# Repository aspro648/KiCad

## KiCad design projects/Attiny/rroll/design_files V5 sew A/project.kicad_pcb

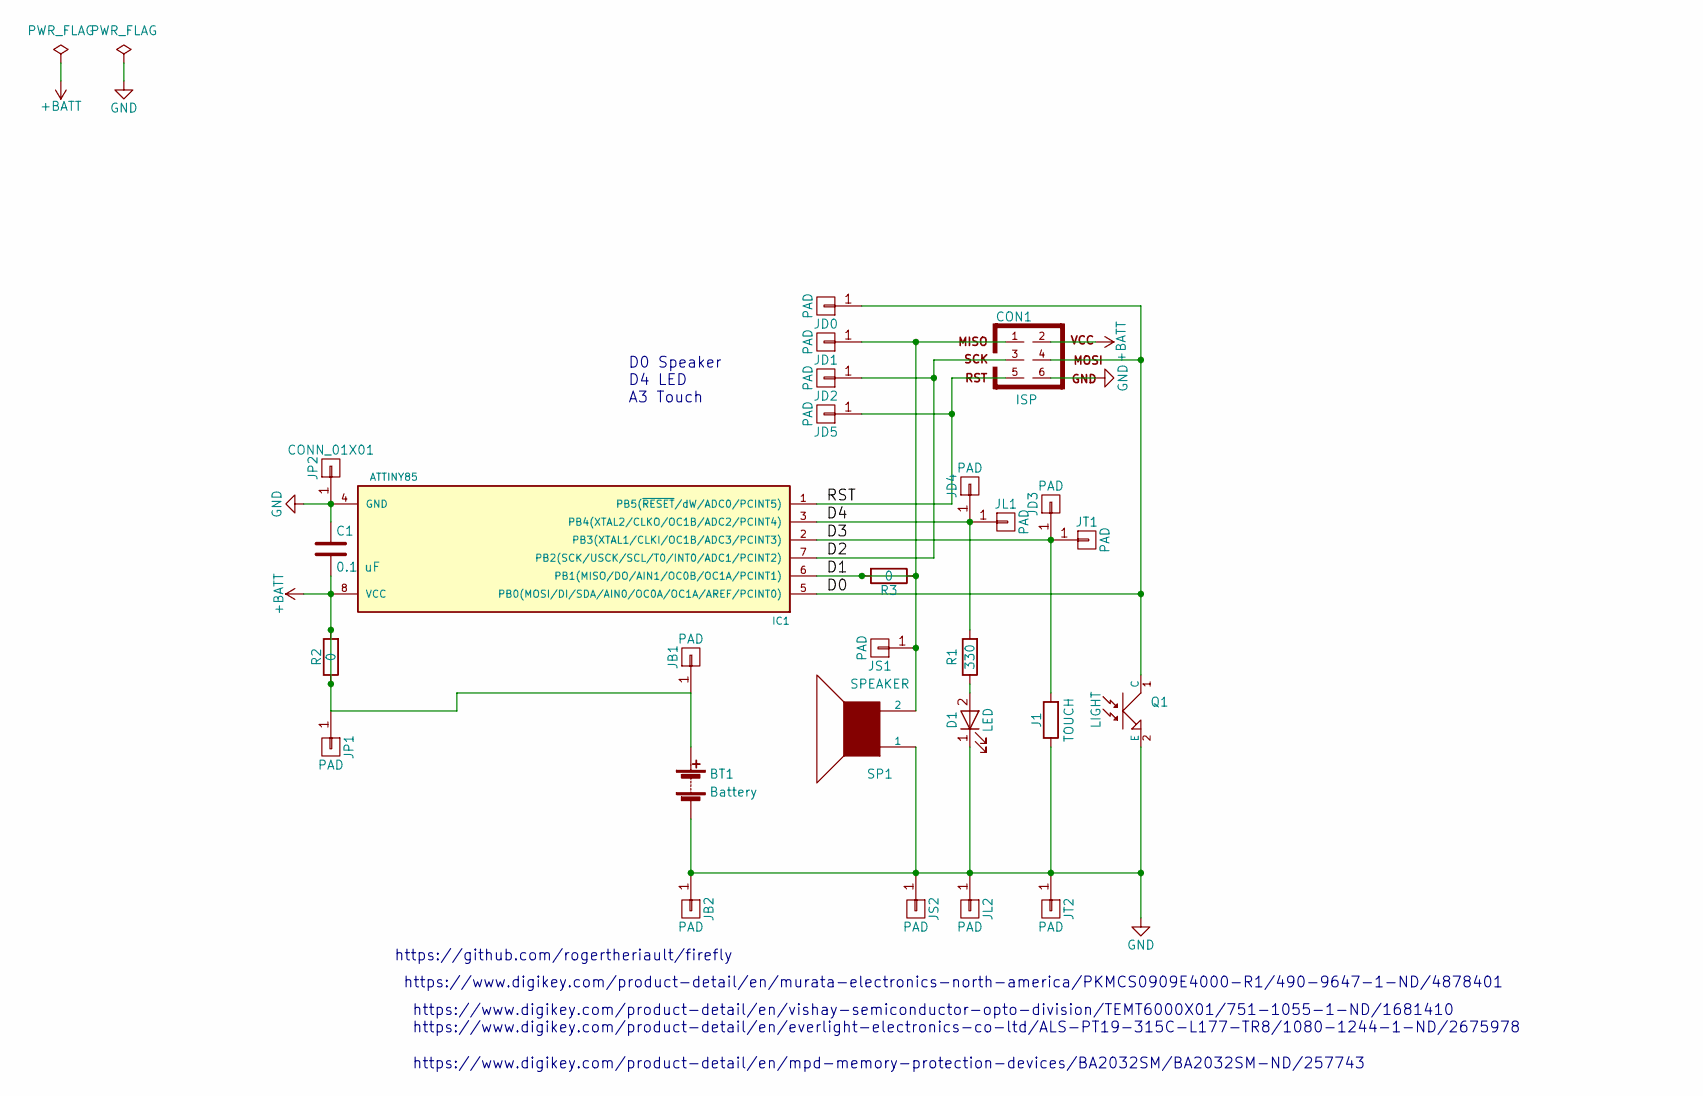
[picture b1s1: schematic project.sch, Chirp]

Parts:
BT1: Battery; BATT_CR2032_SMD
C1: 0.1 uF; C_1206
CON1: ISP; Pin_Header_Straight_2x03_Pitch2.54mm
D1: LED; LED_1206
IC1: ATTINY85; SOIJ-8_5.3x5.3mm_Pitch1.27mm
J1: TOUCH; R_1206_HandSoldering
JB1, JB2: PAD; SewPad
JD0, JD1, JD2, JD3, JD4, JD5: PAD; SewPad
JL1, JL2: PAD; SewPad
JP1: PAD; SewPad
JP2: CONN_01X01; SewPad
JS1, JS2: PAD; SewPad
JT1, JT2: PAD; SewPad
Q1: LIGHT; PhotoDiode_SMD-DIL2_4.5x4
R1: 330; R_1206
R2, R3: 0; R_1206
SP1: SPEAKER; PS1240_piezo

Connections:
+BATT: BT1.1 (+), C1.2, CON1.2, IC1.8 (VCC), JB1.1, JP1.1, R2.1, R2.2; also elsewhere on the board
/D3: IC1.2 (PB3(XTAL1/CLKI/OC1B/ADC3/PCINT3)), J1.2, JD3.1, JT1.1
/D4: IC1.3 (PB4(XTAL2/CLKO/OC1B/ADC2/PCINT4)), JD4.1, JL1.1, R1.2
/MISO: CON1.1, IC1.6 (PB1(MISO/DO/AIN1/OC0B/OC1A/PCINT1)), JD1.1, JS1.1, R3.1, R3.2, SP1.2
/MOSI: CON1.4, IC1.5 (PB0(MOSI/DI/SDA/AIN0/OC0A/OC1A/AREF/PCI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), JD0.1, Q1.1 (C)
/RST: CON1.5, IC1.1 (PB5(~RESET~/dW/ADC0/PCINT5)), JD5.1
/SCK: CON1.3, IC1.7 (PB2(SCK/USCK/SCL/T0/INT0/ADC1/PCINT2)), JD2.1
GND: BT1.2 (-), C1.1, CON1.6, D1.1 (K), IC1.4 (GND), J1.1, JB2.1, JL2.1, JP2.1, JS2.1, JT2.1, Q1.2 (E), SP1.1; also elsewhere on the board
unnamed: D1.2 (A), R1.1

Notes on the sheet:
D0 Speaker D4 LED A3 Touch
https://github.com/rogertheriault/firefly
https://www.digikey.com/product-detail/en/murata-electronics-north-america/PKMCS0909E4000-R1/490-9647-1-ND/4878401
https://www.digikey.com/product-detail/en/vishay-semiconductor-opto-division/TEMT6000X01/751-1055-1-ND/1681410 https://www.digikey.com/product-detail/en/everlight-electronics-co-ltd/ALS-PT19-315C-L177-TR8/1080-1244-1-ND/2675978
https://www.digikey.com/product-detail/en/mpd-memory-protection-devices/BA2032SM/BA2032SM-ND/257743

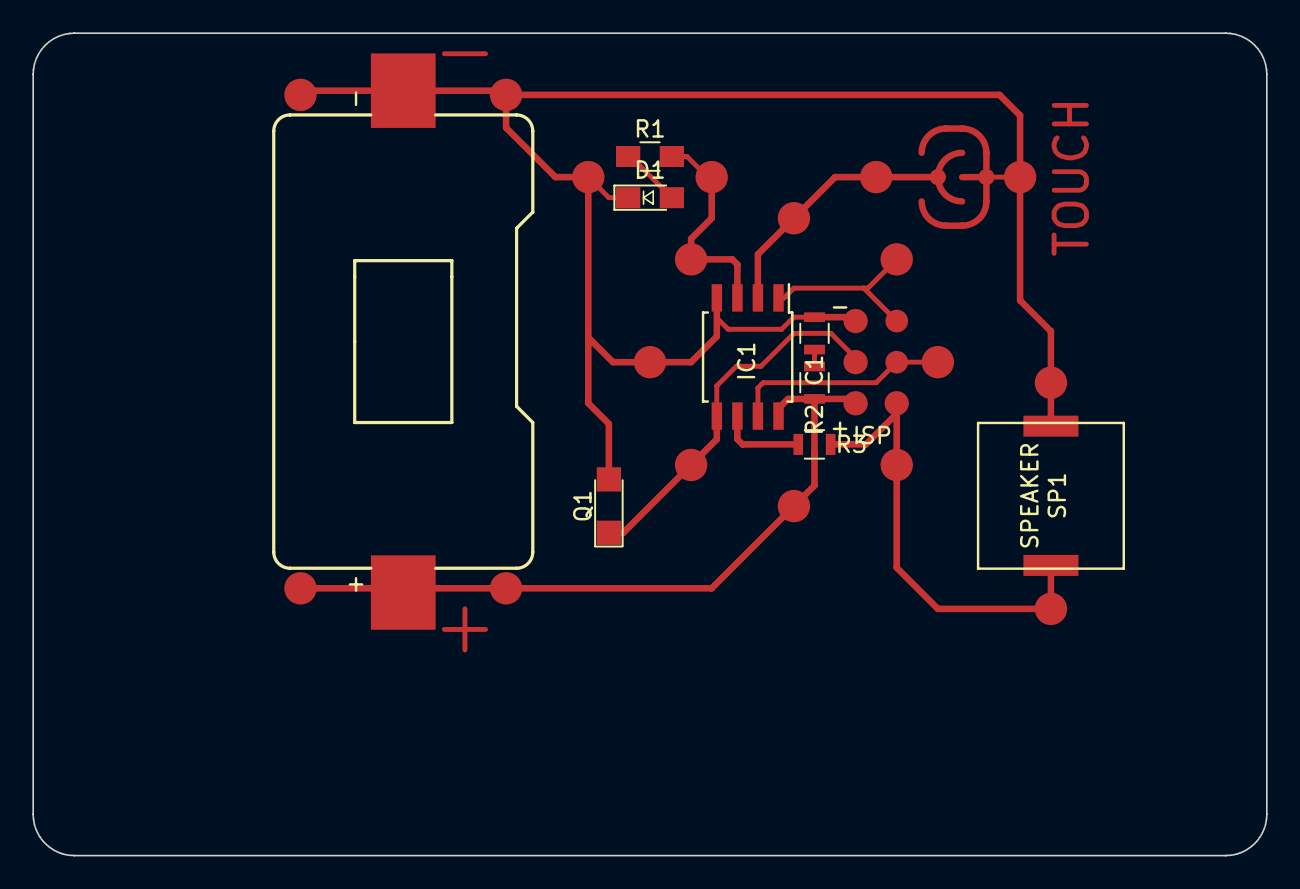
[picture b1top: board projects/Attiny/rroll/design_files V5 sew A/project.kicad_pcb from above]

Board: 2 copper layers, 76.2 x 50.8 mm, 29 parts (0 on the bottom side), 9 nets.

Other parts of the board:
JB1#2, JB2#2: PAD; SewPad

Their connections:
+BATT: JB1#2.1; also elsewhere on the board
GND: JB2#2.1; also elsewhere on the board

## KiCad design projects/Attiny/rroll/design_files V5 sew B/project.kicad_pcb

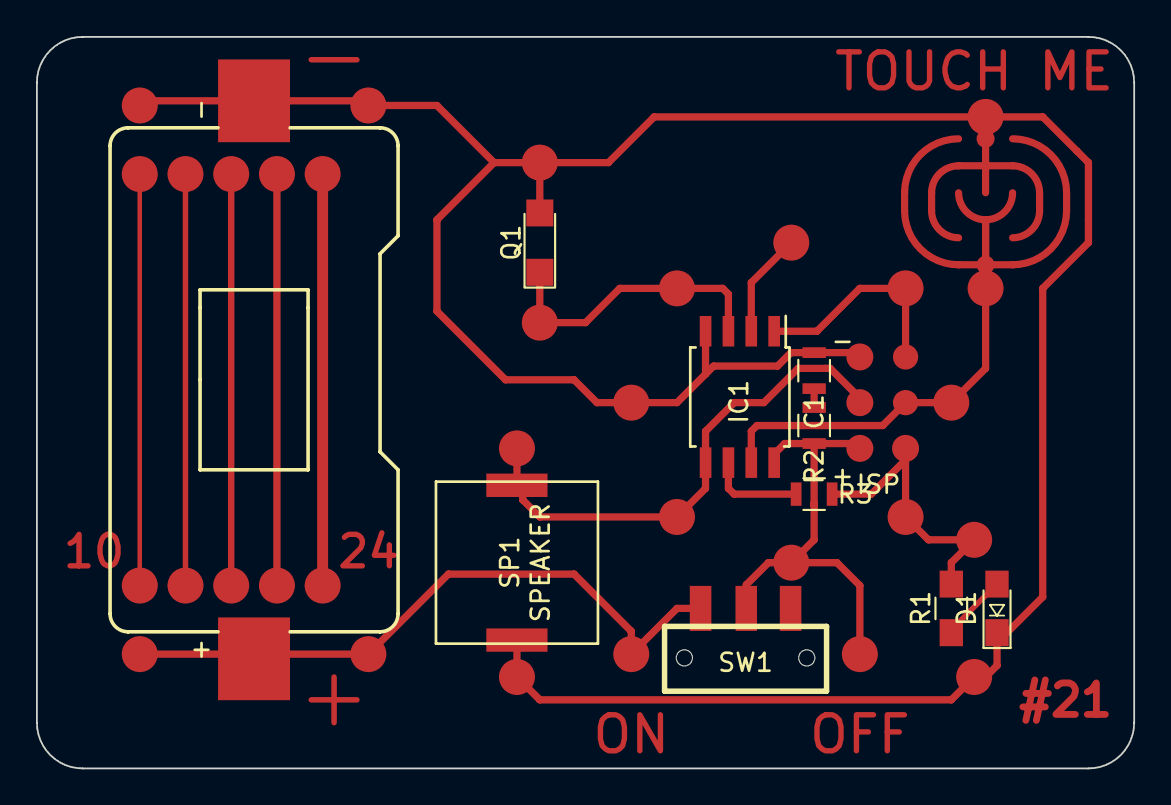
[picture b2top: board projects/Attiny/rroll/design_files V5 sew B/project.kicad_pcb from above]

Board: 2 copper layers, 61.0 x 40.6 mm, 44 parts (0 on the bottom side), 10 nets.

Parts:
BT1: Battery; BATT_BA2032SM
C1: 0.1 uF; R_0805
CON1: ISP; Pin_Header_Straight_2x03_Pitch2.54mm
D1: LED; LED_0805_HandSoldering
IC1: ATTINY85; SOIJ-8_5.3x5.3mm_Pitch1.27mm
J1: TOUCH; SW_SMD_TOUCH
JB1, JB1#2, JB2, JB2#2, JB2#3, JB2#4, JB2#5, JB2#6, JB2#7, JB2#8, JB2#9, JB2#10, JB2#11, JB2#12: PAD; SewPad
JD0, JD1, JD2, JD3, JD4, JD5: PAD; SewPad
JL1, JL2: PAD; SewPad
JP1, JP2: PAD; SewPad
JPT1, JPT2: PAD; SewPad
JS1, JS2: PAD; SewPad
JSW1, JSW2: PAD; SewPad
JT1, JT2: PAD; SewPad
Q1: LIGHT; LED_1206
R1: 330; R_0805_HandSoldering
R2, R3: 0; R_0805
SP1: SPEAKER; PS1240_piezo
SW1: SW_SPDT; SPST_SMD

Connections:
+BATT: C1.2, CON1.2, IC1.8, JP1.1, JSW2.1, R2.1, R2.2, SW1.2
/D0: CON1.4, IC1.5, JD0.1, JS1.1, SP1.2
/D1: CON1.1, IC1.6, JD1.1, JL1.1, R1.2, R3.1, R3.2
/D2: CON1.3, IC1.7, J1.2, JD2.1, JT1.1
/D3: IC1.2, JD3.1
/D4: IC1.3, JD4.1, JPT1.1, Q1.1
/RST: CON1.5, IC1.1, JD5.1
GND: BT1.2, C1.1, CON1.6, D1.1, IC1.4, J1.1, JB2.1, JB2#2.1, JB2#3.1, JB2#4.1, JB2#5.1, JB2#6.1, JB2#7.1, JB2#8.1, JB2#9.1, JB2#10.1, JB2#11.1, JB2#12.1, JL2.1, JP2.1, JPT2.1, JS2.1, JT2.1, Q1.2, SP1.1
unnamed: BT1.1, JB1.1, JB1#2.1, JSW1.1, SW1.1
unnamed: D1.2, R1.1

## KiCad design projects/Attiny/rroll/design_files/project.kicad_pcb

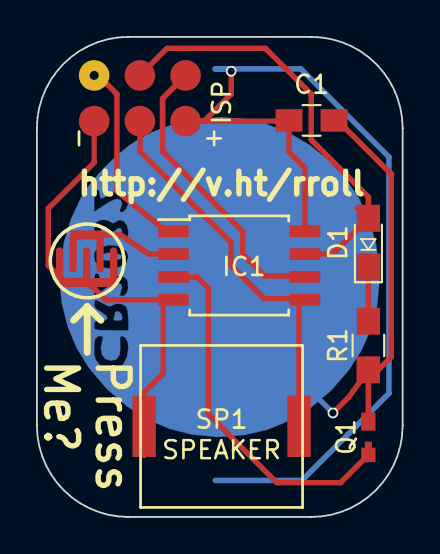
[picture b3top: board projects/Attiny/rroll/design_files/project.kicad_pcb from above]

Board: 2 copper layers, 20.3 x 26.7 mm, 9 parts (1 on the bottom side), 9 nets.

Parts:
BT1: Battery; BATT_CR2032_SMD
C1: 0.1 uF; C_0805_HandSoldering
CON1: ISP; Pin_Header_Straight_2x03_Pitch2.54mm
D1: LED; LED_0805_HandSoldering
IC1: ATTINY85; SOIJ-8_5.3x5.3mm_Pitch1.27mm
J1: JMP; SW_SMD_TOUCH
Q1: LIGHT; PhotoDiode_SMD-DIL2_4.5x4
R1: 330; R_0805_HandSoldering
SP1: SPEAKER; PS1240_piezo

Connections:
+BATT: BT1.1, C1.2, CON1.2, IC1.8
GND: BT1.2, C1.1, CON1.6, IC1.4, J1.1, Q1.2, R1.1, SP1.1
unnamed: CON1.1, IC1.6
unnamed: CON1.3, D1.2, IC1.7
unnamed: CON1.4, IC1.5, SP1.2
unnamed: CON1.5, IC1.1
unnamed: D1.1, R1.2
unnamed: IC1.2, J1.2
unnamed: IC1.3, Q1.1

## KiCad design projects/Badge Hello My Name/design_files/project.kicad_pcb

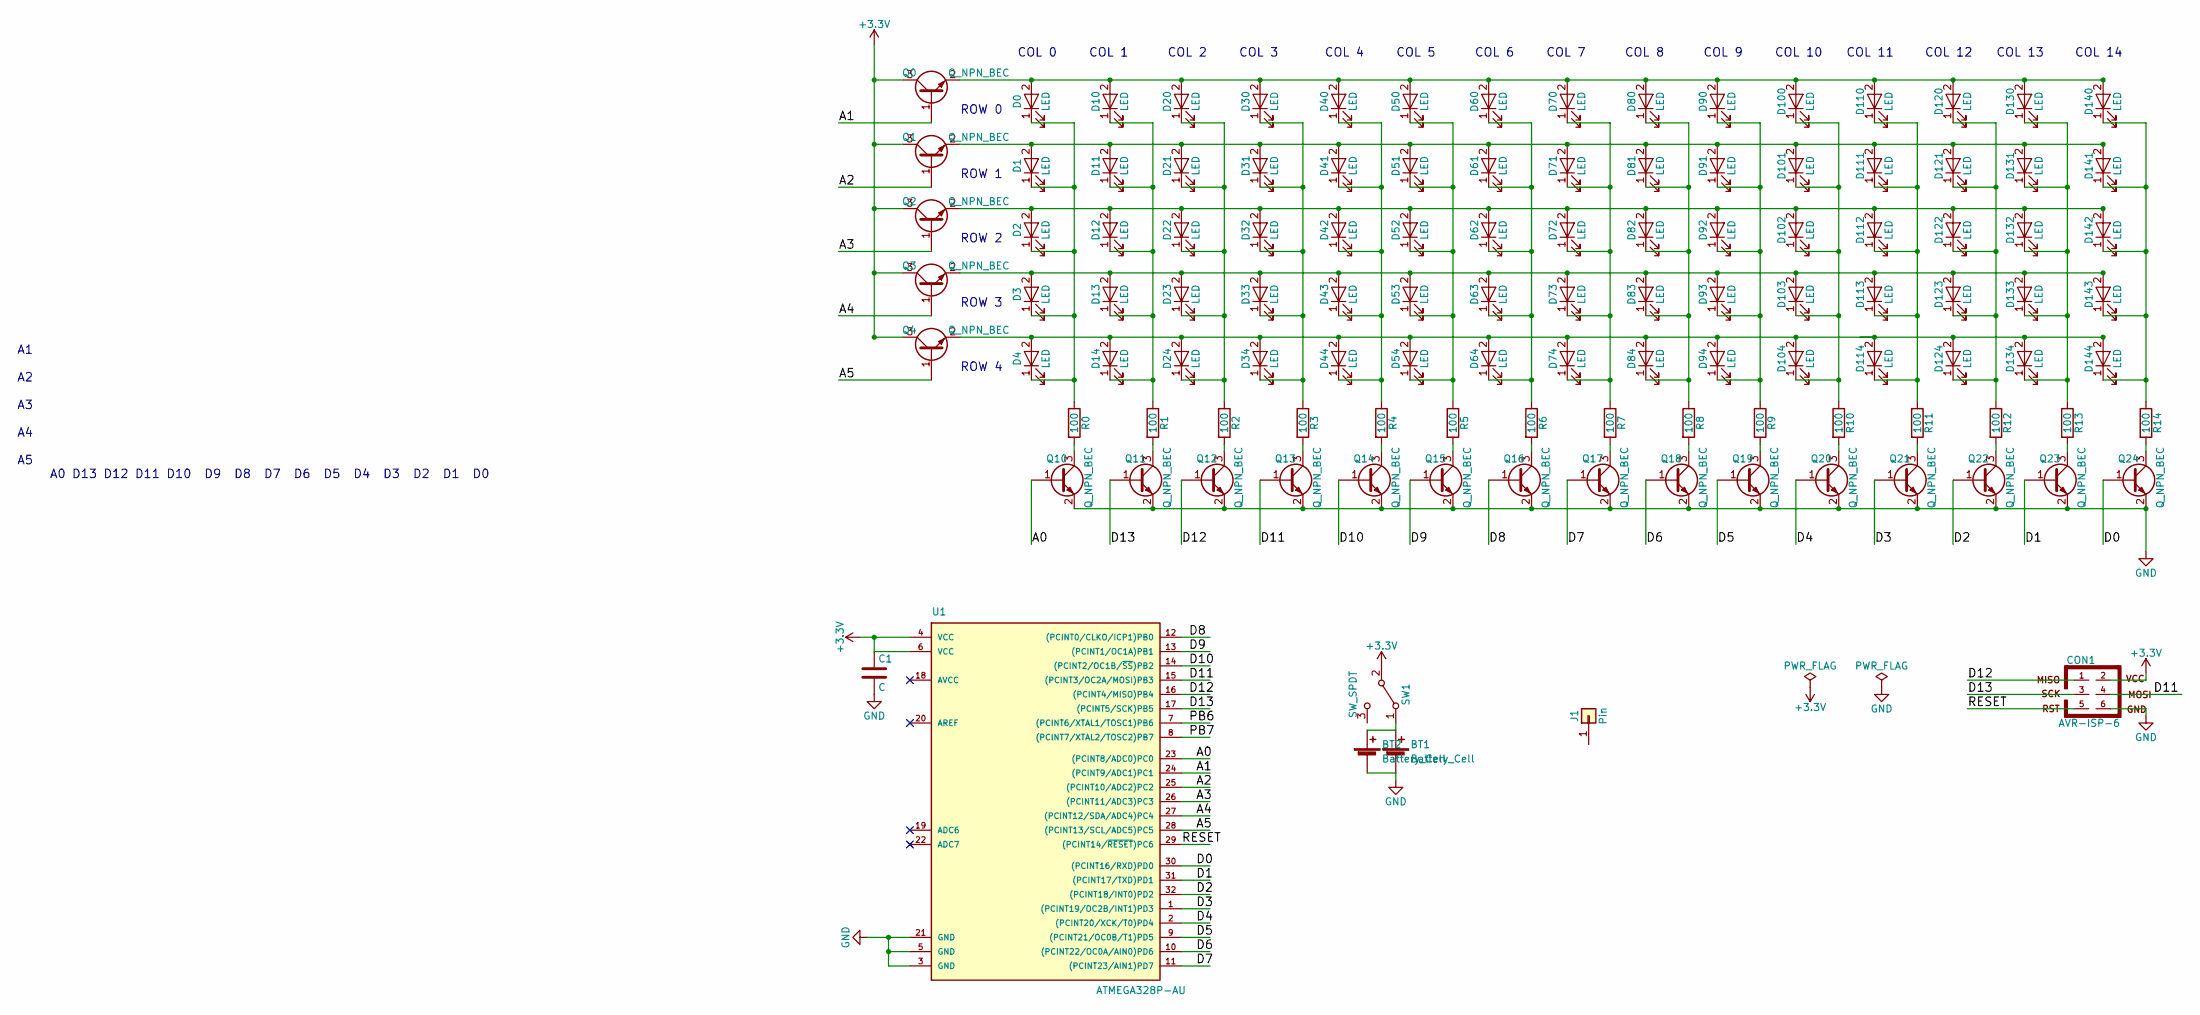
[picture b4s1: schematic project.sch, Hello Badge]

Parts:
BT1, BT2: Battery_Cell; BATT_CR2032_SMD
C1: C; C_0805
CON1: AVR-ISP-6
D0, D1, D2, D3, D4, D10, D11, D12, D13, D14, D20, D21, D22, D23, D24, D30, D31, D32, D33, D34, D40, D41, D42, D43, D44, D50, D51, D52, D53, D54, D60, D61, D62, D63, D64, D70, D71, D72, D73, D74, D80, D81, D82, D83, D84, D90, D91, D92, D93, D94, D100, D101, D102, D103, D104, D110, D111, D112, D113, D114, D120, D121, D122, D123, D124, D130, D131, D132, D133, D134, D140, D141, D142, D143, D144: LED; LED_1206_SHORT
J1: Pin; SolderWirePad_single_SMD_5x10mm
Q0, Q1, Q2, Q3, Q4, Q10, Q11, Q12, Q13, Q14, Q15, Q16, Q17, Q18, Q19, Q20, Q21, Q22, Q23, Q24: Q_NPN_BEC; SOT-23
R0, R1, R2, R3, R4, R5, R6, R7, R8, R9, R10, R11, R12, R13, R14: 100; R_0805
SW1: SW_SPDT; SPST_SMD
U1: ATMEGA328P-AU; TQFP-32_7x7mm_Pitch0.8mm

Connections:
+3V3: C1.1, CON1.2, Q0.3 (C), Q1.3 (C), Q2.3 (C), Q3.3 (C), Q4.3 (C), SW1.2 (B), U1.4 (VCC), U1.6 (VCC)
/A0: Q10.1 (B), U1.23 ((PCINT8/ADC0)PC0)
/A1: Q0.1 (B), U1.24 ((PCINT9/ADC1)PC1)
/A2: Q1.1 (B), U1.25 ((PCINT10/ADC2)PC2)
/A3: Q2.1 (B), U1.26 ((PCINT11/ADC3)PC3)
/A4: Q3.1 (B), U1.27 ((PCINT12/SDA/ADC4)PC4)
/A5: Q4.1 (B), U1.28 ((PCINT13/SCL/ADC5)PC5)
/D0: Q24.1 (B), U1.30 ((PCINT16/RXD)PD0)
/D1: Q23.1 (B), U1.31 ((PCINT17/TXD)PD1)
/D2: Q22.1 (B), U1.32 ((PCINT18/INT0)PD2)
/D3: Q21.1 (B), U1.1 ((PCINT19/OC2B/INT1)PD3)
/D4: Q20.1 (B), U1.2 ((PCINT20/XCK/T0)PD4)
/D5: Q19.1 (B), U1.9 ((PCINT21/OC0B/T1)PD5)
/D6: Q18.1 (B), U1.10 ((PCINT22/OC0A/AIN0)PD6)
/D7: Q17.1 (B), U1.11 ((PCINT23/AIN1)PD7)
/D8: Q16.1 (B), U1.12 ((PCINT0/CLKO/ICP1)PB0)
/D9: Q15.1 (B), U1.13 ((PCINT1/OC1A)PB1)
/D10: Q14.1 (B), U1.14 ((PCINT2/OC1B/~SS~)PB2)
/D11: CON1.4, Q13.1 (B), U1.15 ((PCINT3/OC2A/MOSI)PB3)
/D12: CON1.1, Q12.1 (B), U1.16 ((PCINT4/MISO)PB4)
/D13: CON1.3, Q11.1 (B), U1.17 ((PCINT5/SCK)PB5)
/PB6: U1.7 ((PCINT6/XTAL1/TOSC1)PB6); also elsewhere on the board
/PB7: U1.8 ((PCINT7/XTAL2/TOSC2)PB7)
/RESET: CON1.5, U1.29 ((PCINT14/~RESET~)PC6)
GND: BT1.2 (-), BT2.2 (-), C1.2, CON1.6, Q10.2 (E), Q11.2 (E), Q12.2 (E), Q13.2 (E), Q14.2 (E), Q15.2 (E), Q16.2 (E), Q17.2 (E), Q18.2 (E), Q19.2 (E), Q20.2 (E), Q21.2 (E), Q22.2 (E), Q23.2 (E), Q24.2 (E), U1.3 (GND), U1.5 (GND), U1.21 (GND); also elsewhere on the board
unnamed: BT1.1 (+), BT2.1 (+), SW1.1 (A)
unnamed: D0.1 (K), D1.1 (K), D2.1 (K), D3.1 (K), D4.1 (K), R0.1
unnamed: D0.2 (A), D10.2 (A), D20.2 (A), D30.2 (A), D40.2 (A), D50.2 (A), D60.2 (A), D70.2 (A), D80.2 (A), D90.2 (A), D100.2 (A), D110.2 (A), D120.2 (A), D130.2 (A), D140.2 (A), Q0.2 (E)
unnamed: D1.2 (A), D11.2 (A), D21.2 (A), D31.2 (A), D41.2 (A), D51.2 (A), D61.2 (A), D71.2 (A), D81.2 (A), D91.2 (A), D101.2 (A), D111.2 (A), D121.2 (A), D131.2 (A), D141.2 (A), Q1.2 (E)
unnamed: D10.1 (K), D11.1 (K), D12.1 (K), D13.1 (K), D14.1 (K), R1.1
unnamed: D20.1 (K), D21.1 (K), D22.1 (K), D23.1 (K), D24.1 (K), R2.1
unnamed: D30.1 (K), D31.1 (K), D32.1 (K), D33.1 (K), D34.1 (K), R3.1
unnamed: D40.1 (K), D41.1 (K), D42.1 (K), D43.1 (K), D44.1 (K), R4.1
unnamed: D50.1 (K), D51.1 (K), D52.1 (K), D53.1 (K), D54.1 (K), R5.1
unnamed: D60.1 (K), D61.1 (K), D62.1 (K), D63.1 (K), D64.1 (K), R6.1
unnamed: D70.1 (K), D71.1 (K), D72.1 (K), D73.1 (K), D74.1 (K), R7.1
unnamed: D80.1 (K), D81.1 (K), D82.1 (K), D83.1 (K), D84.1 (K), R8.1
unnamed: D90.1 (K), D91.1 (K), D92.1 (K), D93.1 (K), D94.1 (K), R9.1
unnamed: D100.1 (K), D101.1 (K), D102.1 (K), D103.1 (K), D104.1 (K), R10.1
unnamed: D2.2 (A), D12.2 (A), D22.2 (A), D32.2 (A), D42.2 (A), D52.2 (A), D62.2 (A), D72.2 (A), D82.2 (A), D92.2 (A), D102.2 (A), D112.2 (A), D122.2 (A), D132.2 (A), D142.2 (A), Q2.2 (E)
unnamed: D3.2 (A), D13.2 (A), D23.2 (A), D33.2 (A), D43.2 (A), D53.2 (A), D63.2 (A), D73.2 (A), D83.2 (A), D93.2 (A), D103.2 (A), D113.2 (A), D123.2 (A), D133.2 (A), D143.2 (A), Q3.2 (E)
unnamed: D4.2 (A), D14.2 (A), D24.2 (A), D34.2 (A), D44.2 (A), D54.2 (A), D64.2 (A), D74.2 (A), D84.2 (A), D94.2 (A), D104.2 (A), D114.2 (A), D124.2 (A), D134.2 (A), D144.2 (A), Q4.2 (E)
unnamed: D110.1 (K), D111.1 (K), D112.1 (K), D113.1 (K), D114.1 (K), R11.1
unnamed: D120.1 (K), D121.1 (K), D122.1 (K), D123.1 (K), D124.1 (K), R12.1
unnamed: D130.1 (K), D131.1 (K), D132.1 (K), D133.1 (K), D134.1 (K), R13.1
unnamed: D140.1 (K), D141.1 (K), D142.1 (K), D143.1 (K), D144.1 (K), R14.1
unnamed: Q10.3 (C), R0.2
unnamed: Q11.3 (C), R1.2
unnamed: Q12.3 (C), R2.2
unnamed: Q13.3 (C), R3.2
unnamed: Q14.3 (C), R4.2
unnamed: Q15.3 (C), R5.2
unnamed: Q16.3 (C), R6.2
unnamed: Q17.3 (C), R7.2
unnamed: Q18.3 (C), R8.2
unnamed: Q19.3 (C), R9.2
unnamed: Q20.3 (C), R10.2
unnamed: Q21.3 (C), R11.2
unnamed: Q22.3 (C), R12.2
unnamed: Q23.3 (C), R13.2
unnamed: Q24.3 (C), R14.2

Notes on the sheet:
COL 1
COL 2
COL 3
COL 4
COL 5
COL 6
COL 7
COL 8
ROW 0
ROW 1
ROW 2
ROW 3
ROW 4
COL 0
COL 9
COL 10
COL 11
COL 12
COL 13
COL 14
A1 A2 A3 A4 A5 A0 D13 D12 D11 D10 D9 D8 D7 D6 D5 D4 D3 D2 D1 D0

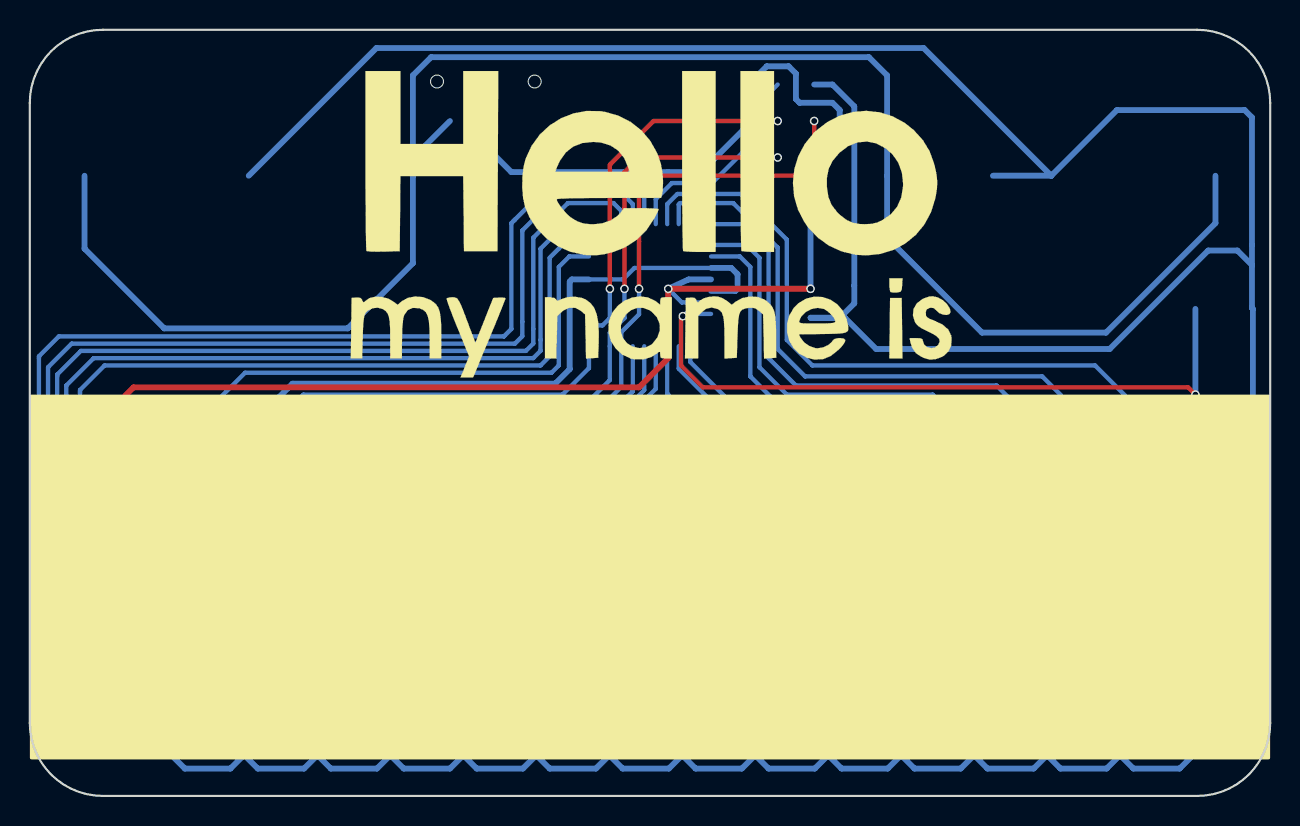
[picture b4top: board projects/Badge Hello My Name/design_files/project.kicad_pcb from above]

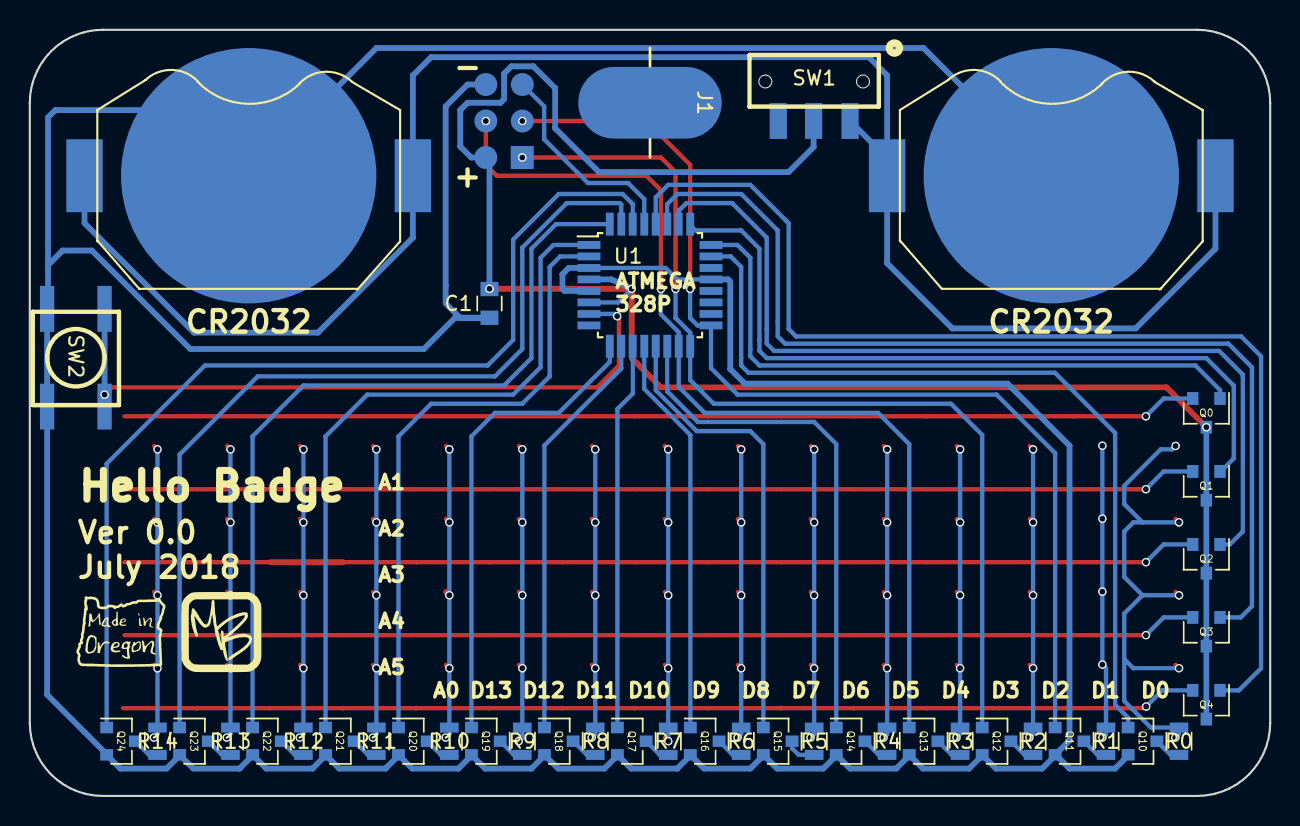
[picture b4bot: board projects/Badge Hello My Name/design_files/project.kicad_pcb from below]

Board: 2 copper layers, 86.4 x 53.3 mm, 120 parts (43 on the bottom side), 60 nets.

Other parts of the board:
SW2: SW_Push; SW_SMD_PUSH
VAL: MadeInOregonRev25
VAL#2: MB225rev

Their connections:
/PB6: SW2.1; also elsewhere on the board
GND: SW2.2; also elsewhere on the board

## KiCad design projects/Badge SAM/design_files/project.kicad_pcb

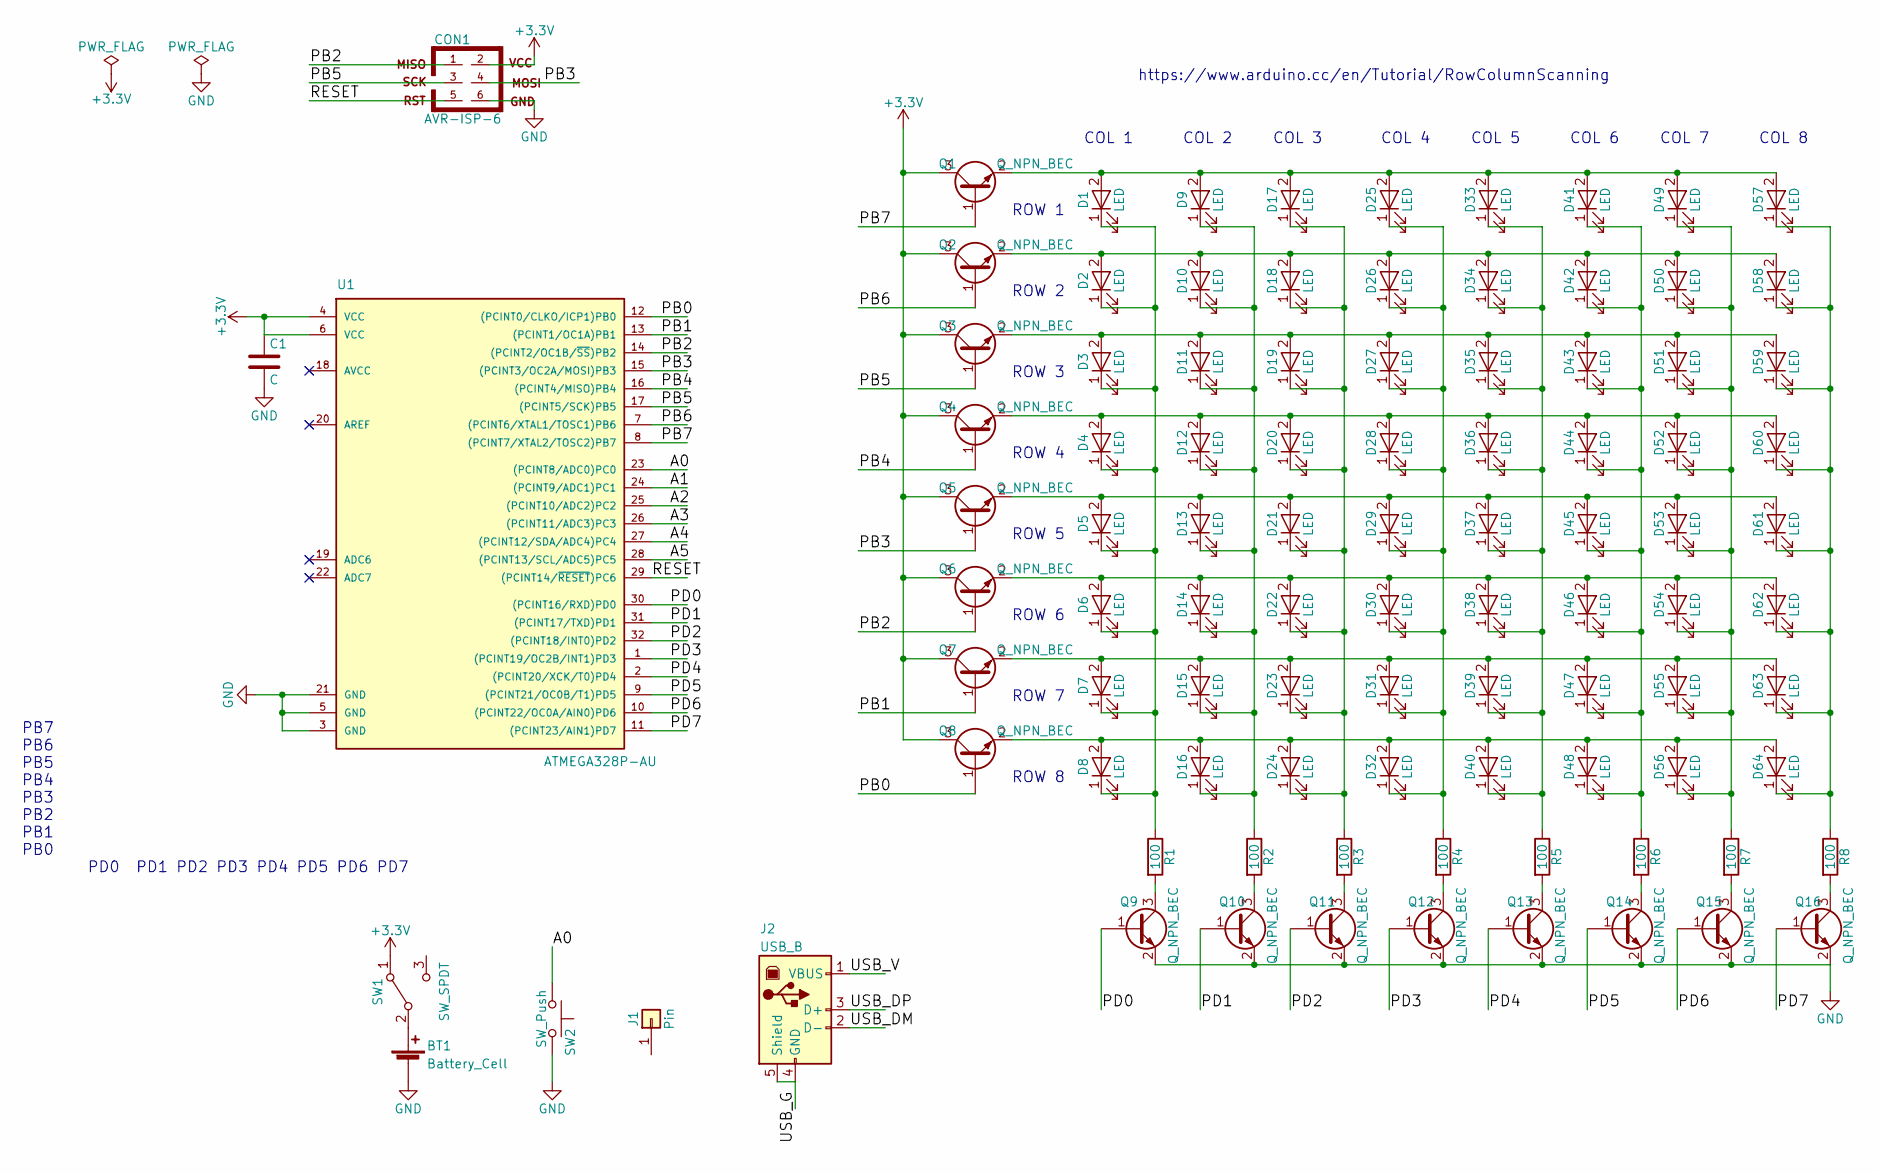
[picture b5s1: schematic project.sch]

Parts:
BT1: Battery_Cell; BATT_CR2032_SMD
C1: C; C_0805
CON1: AVR-ISP-6
D1, D2, D3, D4, D5, D6, D7, D8, D9, D10, D11, D12, D13, D14, D15, D16, D17, D18, D19, D20, D21, D22, D23, D24, D25, D26, D27, D28, D29, D30, D31, D32, D33, D34, D35, D36, D37, D38, D39, D40, D41, D42, D43, D44, D45, D46, D47, D48, D49, D50, D51, D52, D53, D54, D55, D56, D57, D58, D59, D60, D61, D62, D63, D64: LED; LED_0805
J1: Pin; SolderWirePad_single_SMD_5x10mm
J2: USB_B; USB_Micro-B_Wuerth-629105150521
Q1, Q2, Q3, Q4, Q5, Q6, Q7, Q8, Q9, Q10, Q11, Q12, Q13, Q14, Q15, Q16: Q_NPN_BEC; SOT-23
R1, R2, R3, R4, R5, R6, R7, R8: 100; R_0805
SW1: SW_SPDT; SPST_SMD
SW2: SW_Push; SW_SMD_PUSH
U1: ATMEGA328P-AU; TQFP-32_7x7mm_Pitch0.8mm

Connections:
+3V3: C1.1, CON1.2, Q1.3 (C), Q2.3 (C), Q3.3 (C), Q4.3 (C), Q5.3 (C), Q6.3 (C), Q7.3 (C), Q8.3 (C), SW1.1 (A), U1.4 (VCC), U1.6 (VCC)
/A0: SW2.1, U1.23 ((PCINT8/ADC0)PC0)
/A1: U1.24 ((PCINT9/ADC1)PC1)
/A2: U1.25 ((PCINT10/ADC2)PC2)
/A3: U1.26 ((PCINT11/ADC3)PC3)
/A4: U1.27 ((PCINT12/SDA/ADC4)PC4)
/A5: U1.28 ((PCINT13/SCL/ADC5)PC5)
/PB0: Q8.1 (B), U1.12 ((PCINT0/CLKO/ICP1)PB0)
/PB1: Q7.1 (B), U1.13 ((PCINT1/OC1A)PB1)
/PB2: CON1.1, Q6.1 (B), U1.14 ((PCINT2/OC1B/~SS~)PB2)
/PB3: CON1.4, Q5.1 (B), U1.15 ((PCINT3/OC2A/MOSI)PB3)
/PB4: Q4.1 (B), U1.16 ((PCINT4/MISO)PB4)
/PB5: CON1.3, Q3.1 (B), U1.17 ((PCINT5/SCK)PB5)
/PB6: Q2.1 (B), U1.7 ((PCINT6/XTAL1/TOSC1)PB6)
/PB7: Q1.1 (B), U1.8 ((PCINT7/XTAL2/TOSC2)PB7)
/PD0: Q9.1 (B), U1.30 ((PCINT16/RXD)PD0)
/PD1: Q10.1 (B), U1.31 ((PCINT17/TXD)PD1)
/PD2: Q11.1 (B), U1.32 ((PCINT18/INT0)PD2)
/PD3: Q12.1 (B), U1.1 ((PCINT19/OC2B/INT1)PD3)
/PD4: Q13.1 (B), U1.2 ((PCINT20/XCK/T0)PD4)
/PD5: Q14.1 (B), U1.9 ((PCINT21/OC0B/T1)PD5)
/PD6: Q15.1 (B), U1.10 ((PCINT22/OC0A/AIN0)PD6)
/PD7: Q16.1 (B), U1.11 ((PCINT23/AIN1)PD7)
/RESET: CON1.5, U1.29 ((PCINT14/~RESET~)PC6)
/USB_DM: J2.2 (D-)
/USB_DP: J2.3 (D+)
/USB_G: J2.4 (GND), J2.5 (Shield)
/USB_V: J2.1 (VBUS)
GND: BT1.2 (-), C1.2, CON1.6, Q9.2 (E), Q10.2 (E), Q11.2 (E), Q12.2 (E), Q13.2 (E), Q14.2 (E), Q15.2 (E), Q16.2 (E), SW2.2, U1.3 (GND), U1.5 (GND), U1.21 (GND)
unnamed: BT1.1 (+), SW1.2 (B)
unnamed: D1.1 (K), D2.1 (K), D3.1 (K), D4.1 (K), D5.1 (K), D6.1 (K), D7.1 (K), D8.1 (K), R1.1
unnamed: D1.2 (A), D9.2 (A), D17.2 (A), D25.2 (A), D33.2 (A), D41.2 (A), D49.2 (A), D57.2 (A), Q1.2 (E)
unnamed: D9.1 (K), D10.1 (K), D11.1 (K), D12.1 (K), D13.1 (K), D14.1 (K), D15.1 (K), D16.1 (K), R2.1
unnamed: D2.2 (A), D10.2 (A), D18.2 (A), D26.2 (A), D34.2 (A), D42.2 (A), D50.2 (A), D58.2 (A), Q2.2 (E)
unnamed: D3.2 (A), D11.2 (A), D19.2 (A), D27.2 (A), D35.2 (A), D43.2 (A), D51.2 (A), D59.2 (A), Q3.2 (E)
unnamed: D4.2 (A), D12.2 (A), D20.2 (A), D28.2 (A), D36.2 (A), D44.2 (A), D52.2 (A), D60.2 (A), Q4.2 (E)
unnamed: D5.2 (A), D13.2 (A), D21.2 (A), D29.2 (A), D37.2 (A), D45.2 (A), D53.2 (A), D61.2 (A), Q5.2 (E)
unnamed: D6.2 (A), D14.2 (A), D22.2 (A), D30.2 (A), D38.2 (A), D46.2 (A), D54.2 (A), D62.2 (A), Q6.2 (E)
unnamed: D7.2 (A), D15.2 (A), D23.2 (A), D31.2 (A), D39.2 (A), D47.2 (A), D55.2 (A), D63.2 (A), Q7.2 (E)
unnamed: D8.2 (A), D16.2 (A), D24.2 (A), D32.2 (A), D40.2 (A), D48.2 (A), D56.2 (A), D64.2 (A), Q8.2 (E)
unnamed: D17.1 (K), D18.1 (K), D19.1 (K), D20.1 (K), D21.1 (K), D22.1 (K), D23.1 (K), D24.1 (K), R3.1
unnamed: D25.1 (K), D26.1 (K), D27.1 (K), D28.1 (K), D29.1 (K), D30.1 (K), D31.1 (K), D32.1 (K), R4.1
unnamed: D33.1 (K), D34.1 (K), D35.1 (K), D36.1 (K), D37.1 (K), D38.1 (K), D39.1 (K), D40.1 (K), R5.1
unnamed: D41.1 (K), D42.1 (K), D43.1 (K), D44.1 (K), D45.1 (K), D46.1 (K), D47.1 (K), D48.1 (K), R6.1
unnamed: D49.1 (K), D50.1 (K), D51.1 (K), D52.1 (K), D53.1 (K), D54.1 (K), D55.1 (K), D56.1 (K), R7.1
unnamed: D57.1 (K), D58.1 (K), D59.1 (K), D60.1 (K), D61.1 (K), D62.1 (K), D63.1 (K), D64.1 (K), R8.1
unnamed: Q9.3 (C), R1.2
unnamed: Q10.3 (C), R2.2
unnamed: Q11.3 (C), R3.2
unnamed: Q12.3 (C), R4.2
unnamed: Q13.3 (C), R5.2
unnamed: Q14.3 (C), R6.2
unnamed: Q15.3 (C), R7.2
unnamed: Q16.3 (C), R8.2

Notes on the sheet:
https://www.arduino.cc/en/Tutorial/RowColumnScanning
COL 1
COL 2
COL 3
COL 4
COL 5
COL 6
COL 7
COL 8
ROW 1
ROW 2
ROW 3
ROW 4
ROW 5
ROW 6
ROW 7
ROW 8
PB7 PB6 PB5 PB4 PB3 PB2 PB1 PB0 PD0 PD1 PD2 PD3 PD4 PD5 PD6 PD7

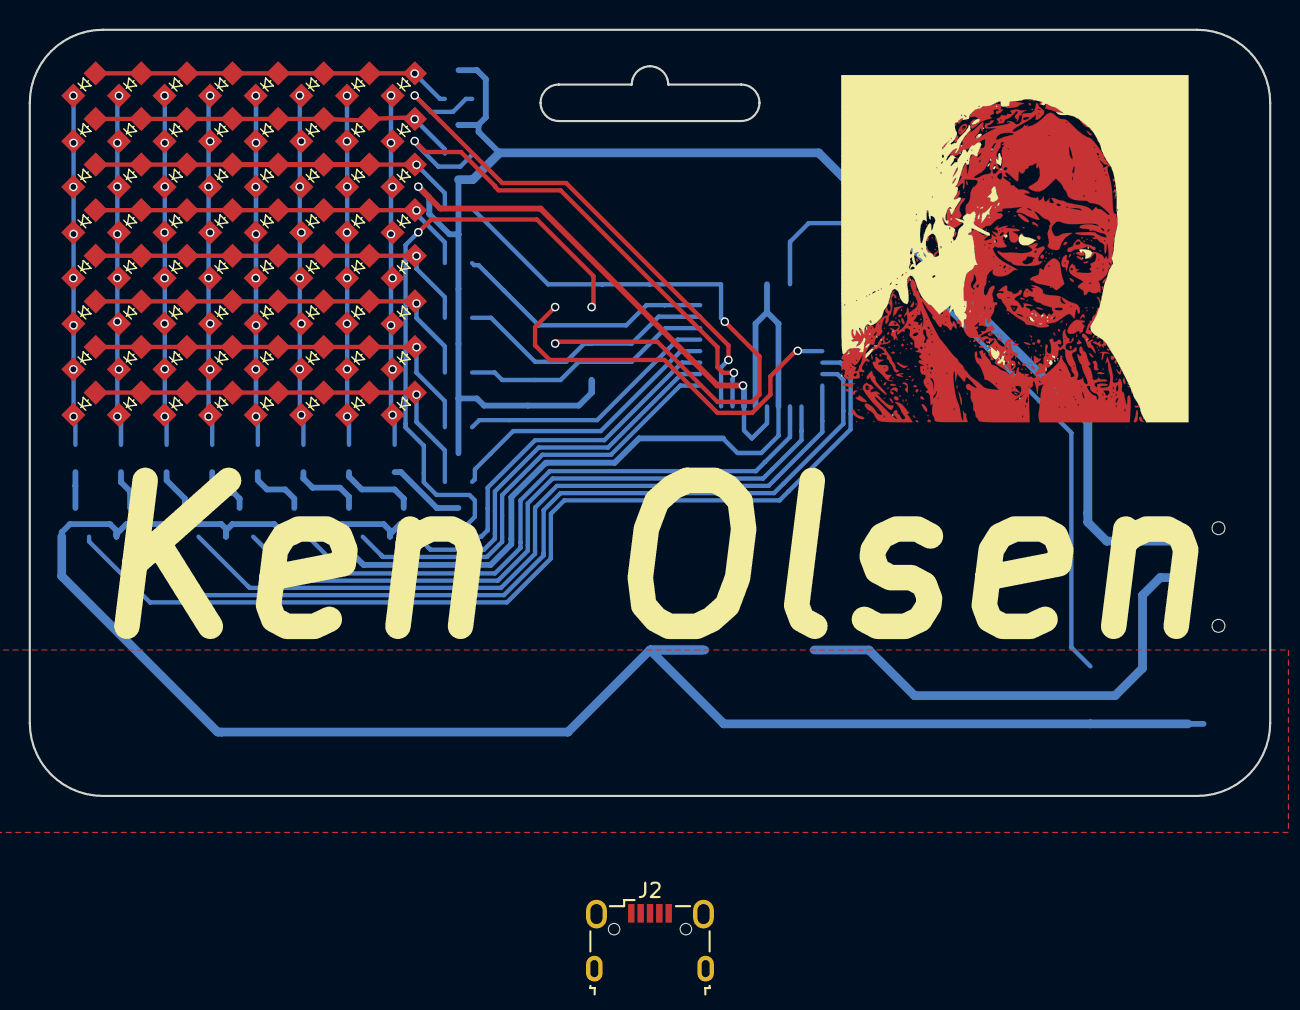
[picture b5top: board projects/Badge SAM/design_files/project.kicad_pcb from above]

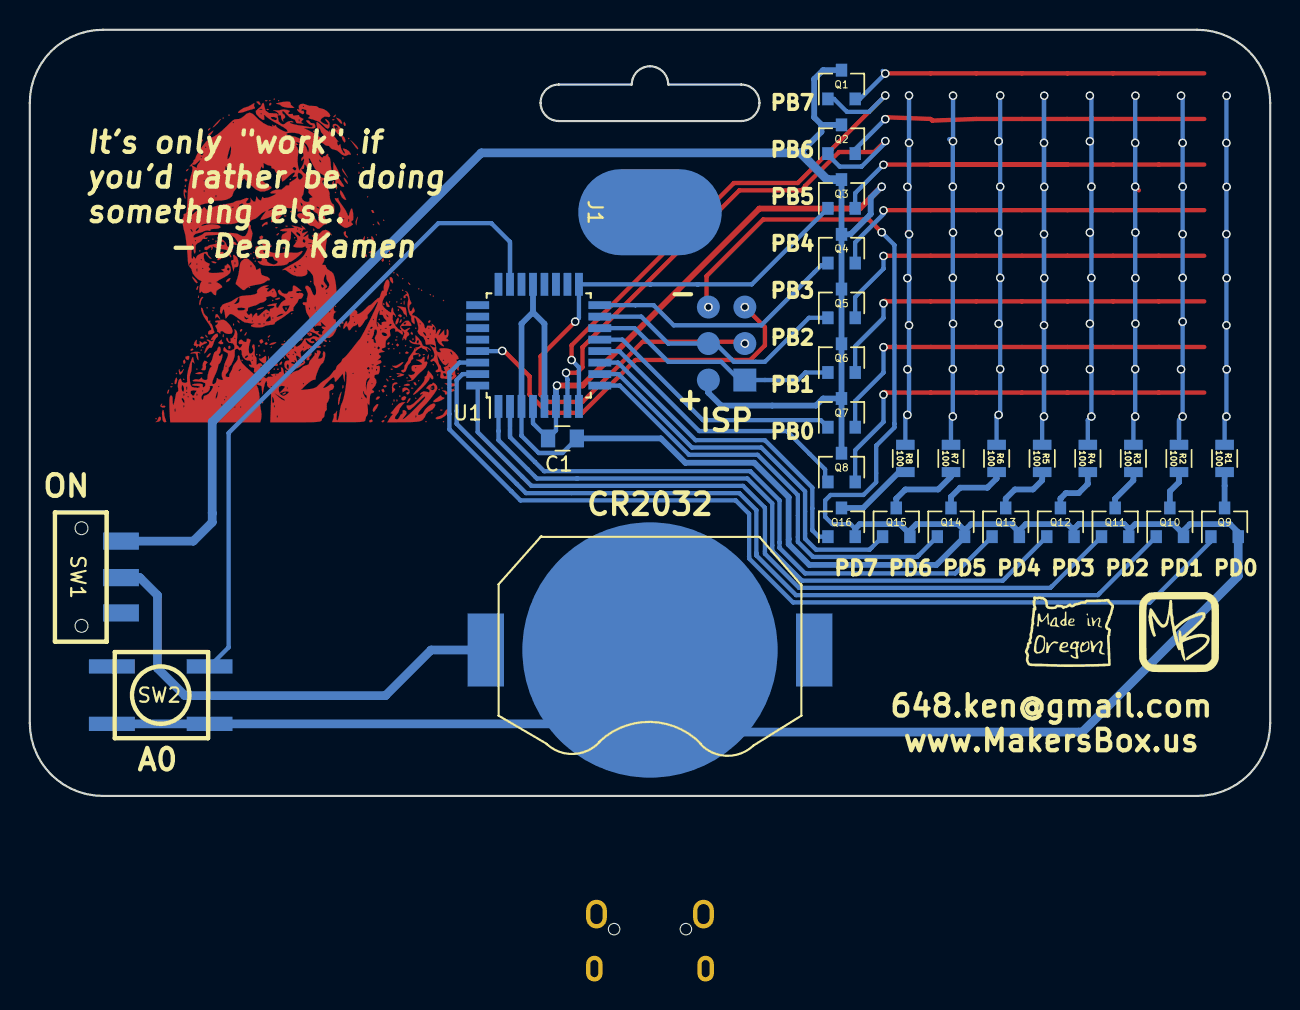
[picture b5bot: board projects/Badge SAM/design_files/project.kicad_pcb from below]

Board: 2 copper layers, 86.4 x 53.3 mm, 98 parts (31 on the bottom side), 46 nets.

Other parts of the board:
VAL: MB225rev
VAL#2: MadeInOregonRev25
